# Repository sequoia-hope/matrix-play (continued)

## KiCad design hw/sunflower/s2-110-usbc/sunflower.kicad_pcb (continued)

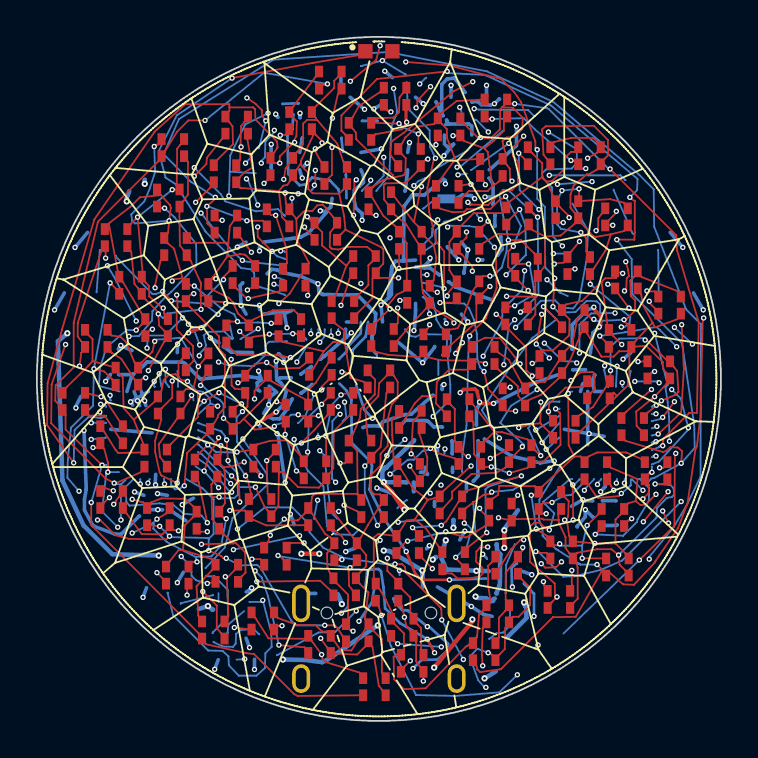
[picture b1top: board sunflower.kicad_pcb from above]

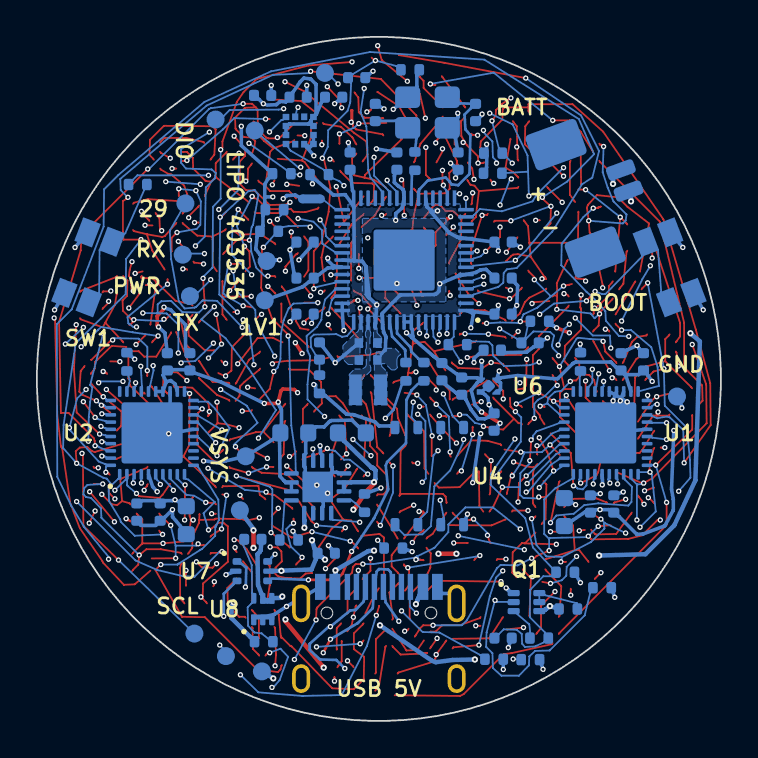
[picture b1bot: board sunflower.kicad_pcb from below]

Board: 4 copper layers, 38.0 x 38.0 mm, 206 parts (95 on the bottom side), 108 nets.

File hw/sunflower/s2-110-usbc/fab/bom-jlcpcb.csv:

Comment,Designator,Footprint,LCSC Part #,MPN,Manufacturer
PicoBlade 2P,BT1,Molex_PicoBlade_53261-0271_1x02-1MP_P1.25mm_Horizontal,C177225,53261-0271,Molex
1u,"C1,C3,C4,C31,C34,C41,C44",C_0402_1005Metric,C52923,CL05A105KA5NQNC,Samsung Electro-Mechanics
22u,"C2,C30,C40",C_0603_1608Metric,C86295,CL10A226MP8NUNE,Samsung Electro-Mechanics
10u,C5,C_0603_1608Metric,C19702,CL10A106KP8NNNC,Samsung Electro-Mechanics
100n,"C6,C7,C8,C9,C10,C11,C12,C13,C14,C20,C21,C22,C25,C27,C32,C33,C35,C42,C43,C70",C_0402_1005Metric,C1525,CL05B104KO5NNNC,Samsung Electro-Mechanics
4.7u,"C16,C18",C_0402_1005Metric_small_pads,C23733,CL05A475MP5NRNC,Samsung Electro-Mechanics
4.7u,"C17,C19,C26",C_0402_1005Metric,C23733,CL05A475MP5NRNC,Samsung Electro-Mechanics
15p,"C23,C24",C_0402_1005Metric,C1548,0402CG150J500NT,FH
RGB,"D1,D2,D3,D4,D5,D6,D7,D8,D9,D10,D11,D12,D13,D14,D15,D16,D17,D18,D19,D20,D21,D22,D23,D24,D25,D26,D27,D28,D29,D30,D31,D32,D33,D34,D35,D36,D37,D38,D39,D40,D41,D42,D43,D44,D45,D46,D47,D48,D49,D50,D51,D52,D53,D54,D55,D56,D57,D58,D59,D60,D61,D62,D63,D64,D65,D66,D67,D68,D69,D70,D71,D72,D73,D74,D75,D76,D77,D78,D79,D80,D81,D82,D83,D84,D85,D86,D87,D88,D89,D90,D91,D92,D93,D94,D95,D96,D97,D98,D99,D100,D101,D102,D103,D104,D105,D106,D107,D108,D109,D110",LED_XL-1615RGBC,C965840,XL-1615RGBC-RF,XINGLIGHT
USB-C,J1,USB_C_Receptacle_HRO_TYPE-C-31-M-12,C165948,TYPE-C-31-M-12,Korean Hroparts Elec
3.3u,L1,L_pol_2016,C42411119,AOTA-B201610S3R3-101-T,Abracon
NTZD3155C,Q1,SOT-563,C236117,NTZD3155CT1G,onsemi
XYC-PT19C-L1,Q2,SENSOR_ALS-PT19,C2693594,XYC-PT19C-L1,NEWOPTO
5.1k,"R1,R2",R_0402_1005Metric,C25905,0402WGF5101TCE,UNI-ROYAL
10k,R3,R_0402_1005Metric,C25744,0402WGF1002TCE,UNI-ROYAL
3k,R4,R_0402_1005Metric,C25784,0402WGF3001TCE,UNI-ROYAL
3.6k,R5,R_0402_1005Metric,C25891,0402WGF3601TCE,UNI-ROYAL
100k,"R6,R7,R9,R10,R11,R12,R31",R_0402_1005Metric,C25741,0402WGF1003TCE,UNI-ROYAL
100R,R8,R_0402_1005Metric,C25076,0402WGF1000TCE,UNI-ROYAL
33R,R13,R_0402_1005Metric,C25105,0402WGF330JTCE,UNI-ROYAL
27R,"R14,R15",R_0402_1005Metric,C25100,0402WGF270JTCE,UNI-ROYAL
1k,"R16,R17,R18,R21,R22",R_0402_1005Metric,C11702,0402WGF1001TCE,UNI-ROYAL
4.7k,"R19,R20",R_0402_1005Metric,C25900,0402WGF4701TCE,UNI-ROYAL
30k,"R30,R33",R_0402_1005Metric,C25776,0402WGF3002TCE,UNI-ROYAL
22k,R43,R_0402_1005Metric,C25768,0402WGF2202TCE,UNI-ROYAL
USER / WAKE,SW1,SW_Panasonic_EVQP7J,C2828254,EVQP7J01P,PANASONIC
BOOTSEL,SW2,SW_Panasonic_EVQP7J,C2828254,EVQP7J01P,PANASONIC
AW20198QNR,"U1,U2",AW20198_QFN-40-1EP_5x5mm_P0.4mm_EP3.4x3.4mm,C5137654,AW20198QNR,Shanghai Awinic Tech
RP2350A,U3,RP2350-QFN-60-1EP_7x7_P0.4mm_EP3.4x3.4mm_ThermalVias,C42411118,RP2350A,Raspberry Pi
W25Q128JVPIQ,U4,WSON-8_6x5mm_P1.27mm_NoEPCopper,C190862,W25Q128JVPIQ,Winbond
BQ24073,U5,QFN-16-1EP_3x3mm_P0.5mm_EP1.7x1.7mm,C15220,BQ24073RGTR,Texas Instruments
TPS7A0233,U6,Texas_X2SON-4_1x1mm_P0.65mm,C2860046,TPS7A0233PDQNR,Texas Instruments
USBLC6-2P6,U7,SOT-666,C15999,USBLC6-2P6,STMicroelectronics
XB9901A,U8,XySemi_DFN-6_1.8x1.4mm,C669687,XB9901A,XySemi
LIS2DW12,U9,LGA-12_2x2mm_P0.5mm,C189624,LIS2DW12TR,STMicroelectronics
12MHz,Y1,Crystal_SMD_3225-4Pin_3.2x2.5mm,C20625731,ABM8-272-T3,Abracon
